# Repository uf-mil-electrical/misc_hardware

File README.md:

# misc_hardware
PCB stuff that doesn't belong to any specific robot

## Projects by type:
### Communication
- [Peter Feng] MCP2515 CAN Bus Module Testing

### LEDs
- [Erik Neff-Flahan] 8x8 Neopixel Matrix V1
- [Russell MacGregor] 8x8 Neopixel Matrix V2
- [Russell MacGregor] Neopixel Breakout Board
- [Erik Neff-Flahan] Neopixel RP2350 C Library

### Logic
- [Russell MacGregor] Level Shifter Breakout V1

### Navigation
- [Russell MacGregor] IMU Test Board V1 (incomplete)

### Power
- [Russell MacGregor] 3V3 1.5A Regulator Breakout
- [Russell MacGregor] Battery ORing Test Board V1
- [Erik Neff-Flahan] RobotX Buoy Board Power Setup
- [Russell MacGregor] Inductor Breakout V1
- [Russell MacGregor] MAX20408 Breakout V1
- [Russell MacGregor] TPS26631 E-Fuse Breakout V1

### RobotX2026
- [Aiden Shepler] Task 2 Props (underwater LEDs)

### Sensing
- [Russell MacGregor] Air Quality Monitor V1
- [Russell MacGregor] Atmospheric Monitor V1
- [Russell MacGregor] Door Sensor V3

### USB
- [Russell MacGregor] USB 2.0 Hub Breakout V4

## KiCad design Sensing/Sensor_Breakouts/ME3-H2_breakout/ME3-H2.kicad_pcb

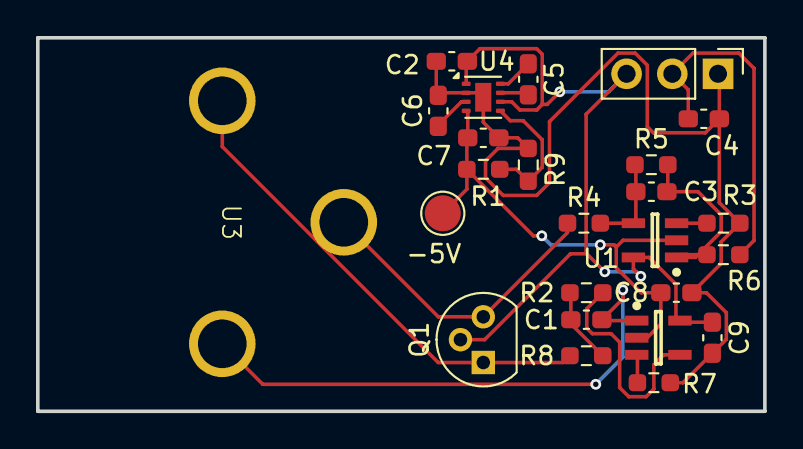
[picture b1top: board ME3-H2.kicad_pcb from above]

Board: 2 copper layers, 40.4 x 20.8 mm, 25 parts (0 on the bottom side), 17 nets.

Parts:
C1, C4, C8, C9: 0.1uF; C_0603_1608Metric_Pad1.08x0.95mm_HandSolder
C2, C3, C6: 4.7uF; C_0603_1608Metric_Pad1.08x0.95mm_HandSolder
C5: 1uF; C_0603_1608Metric_Pad1.08x0.95mm_HandSolder
C7: 2.2uF; C_0603_1608Metric_Pad1.08x0.95mm_HandSolder
J1: Conn_01x03_Pin; PinHeader_1x03_P2.54mm_Vertical
Q1: PJFET; TO-92
R1: 158k; R_0603_1608Metric_Pad0.98x0.95mm_HandSolder
R2, R3, R7, R8: 10k; R_0603_1608Metric_Pad0.98x0.95mm_HandSolder
R4: 47; R_0603_1608Metric_Pad0.98x0.95mm_HandSolder
R5: 30k; R_0603_1608Metric_Pad0.98x0.95mm_HandSolder
R6: 100k; R_0603_1608Metric_Pad0.98x0.95mm_HandSolder
R9: 51k; R_0603_1608Metric_Pad0.98x0.95mm_HandSolder
TP1: -5V; TestPoint_Pad_D2.0mm
U1, U2: LT6003HS5TRPBF; LT-S5-5-TSOT-23_N
U3: ME3-H2
U4: LM27761; WSON-8-1EP_2x2mm_P0.5mm_EP0.9x1.6mm

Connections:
+5V: C2.2, C9.2, J1.3, Q1.2 (G), U1.5 (V+), U2.5 (V+), U4.1 (VIN), U4.6 (EN)
-5V: C7.2, C8.2, R1.1, TP1.1, U1.2 (V-), U2.2 (V-), U4.4 (VOUT)
/Counter: C1.2, U2.1 (OUT), U3.3 (Counter)
/Reference: Q1.1 (D), R8.1, U3.2 (Reference)
/Vout: C4.2, J1.2, R6.2
/Working: Q1.3 (S), R4.1, U3.1 (Working)
GND: C2.1, C4.1, C6.2, C7.1, C8.1, C9.1, J1.1, R3.2, R7.2, R9.2, U4.2 (GND), U4.9 (PAD)
unnamed: C1.1, R2.1, R8.2
unnamed: R3.1, U1.3 (+IN)
unnamed: C3.1, R4.2, R5.1, U1.4 (-IN)
unnamed: C3.2, R5.2, R6.1, U1.1 (OUT)
unnamed: R7.1, U2.3 (+IN)
unnamed: R2.2, U2.4 (-IN)
unnamed: C5.1, U4.8 (C+)
unnamed: C5.2, U4.7 (C-)
unnamed: C6.1, U4.3 (CPOUT)
unnamed: R1.2, R9.1, U4.5 (VFB)

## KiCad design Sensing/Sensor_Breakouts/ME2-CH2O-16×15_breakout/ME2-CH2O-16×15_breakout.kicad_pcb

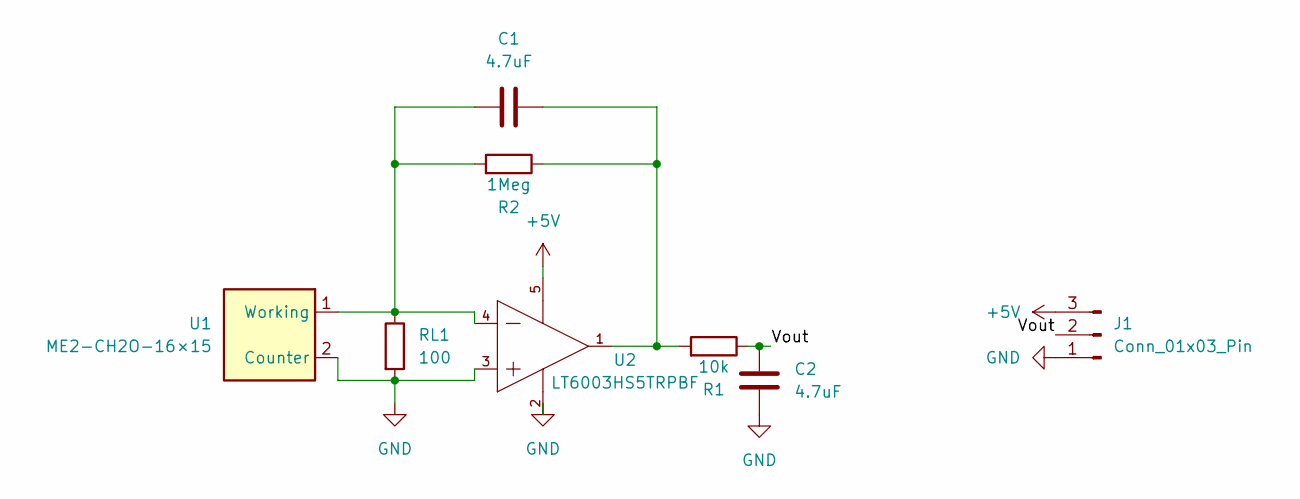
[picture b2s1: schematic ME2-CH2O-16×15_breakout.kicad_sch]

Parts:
C1, C2: 4.7uF; C_0603_1608Metric_Pad1.08x0.95mm_HandSolder
J1: Conn_01x03_Pin; PinHeader_1x03_P2.54mm_Vertical
R1: 10k; R_0603_1608Metric_Pad0.98x0.95mm_HandSolder
R2: 1Meg; R_0603_1608Metric_Pad0.98x0.95mm_HandSolder
RL1: 100; R_0603_1608Metric_Pad0.98x0.95mm_HandSolder
U1: ME2-CH2O-16×15
U2: LT6003HS5TRPBF; LT-S5-5-TSOT-23_N

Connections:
+5V: J1.3, U2.5 (V+)
/Vout: C2.2, J1.2, R1.1
GND: C2.1, J1.1, RL1.2, U1.2 (Counter), U2.2 (V-), U2.3 (+IN)
unnamed: C1.1, R2.2, RL1.1, U1.1 (Working), U2.4 (-IN)
unnamed: C1.2, R1.2, R2.1, U2.1 (OUT)

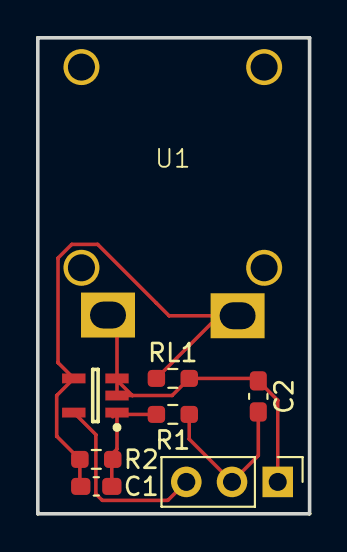
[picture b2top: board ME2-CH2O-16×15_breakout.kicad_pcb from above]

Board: 2 copper layers, 15.1 x 26.4 mm, 8 parts (0 on the bottom side), 5 nets.

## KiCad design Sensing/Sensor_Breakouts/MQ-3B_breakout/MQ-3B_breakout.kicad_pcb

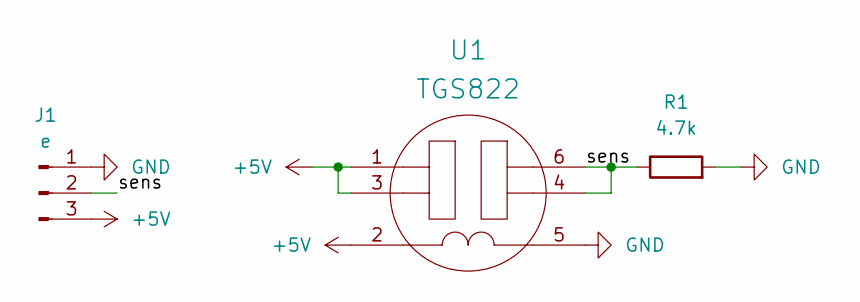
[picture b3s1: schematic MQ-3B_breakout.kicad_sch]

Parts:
J1: e; PinHeader_1x03_P2.54mm_Vertical
R1: 4.7k; R_Axial_DIN0207_L6.3mm_D2.5mm_P7.62mm_Horizontal
U1: TGS822; FP-TGS822-MFG

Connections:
+5V: J1.3, U1.1 (VC), U1.2 (VH), U1.3 (VC)
/sens: J1.2, R1.1, U1.4 (VRL), U1.6 (VRL)
GND: J1.1, R1.2, U1.5 (GND)

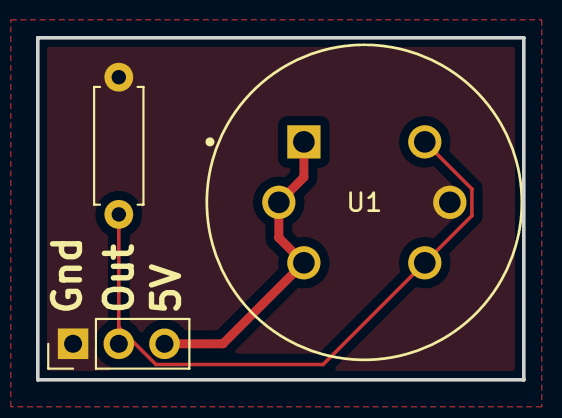
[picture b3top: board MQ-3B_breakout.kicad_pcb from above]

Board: 2 copper layers, 27.0 x 19.0 mm, 3 parts (0 on the bottom side), 3 nets.

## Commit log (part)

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2025-09-22 Finished Door Sensor Board V1
    ye
2025-09-29 09/29 Update
2025-10-08 Generated fabrication files
2025-11-09 Start working on Servo tester code
2025-11-13 Added SSD1306 drivers and tested it
2025-11-13 Cleaned up project, can now draw pulse on the screen
2025-12-04 completed revision of board
    - now uses Pico 2W instead of ESP-32 WROOM board
    - should resolve all issues
2025-12-05 Finalized BOM for ordering parts
2025-12-05 generated excel bom
2025-12-30 Started programming V2
2026-01-06 FINALLY FINALLY FINALLY TOF WORKS YAY
2026-01-06 deleted unnecessary files
2026-01-15 work in progress
2026-01-15 better work in progress
2026-01-15 readded non-wireless code back to repo
2026-01-15 last backup commit i promise
2026-01-15 just kidding last backup frfr
2026-01-15 started modification of CMakeList.txt
    works so far...
2026-01-15 updated CMakeTxt, haven't yet changed project name
2026-01-15 changed project name yay!
2026-01-15 changed file name
2026-01-15 created new file for BLE-relevant functions
    just don't include temp_sensor.h there, it doesn't like that
2026-01-15 untested but compiles
2026-01-16 Created advertisement broadcast design
2026-01-16 figuring things out!
2026-01-16 starting to rework functional program
2026-01-16 restarted cuz bluetooth le explorer is silly
2026-01-16 functional CMakelist file with all libraries and program files added in
2026-01-16 so far so good
2026-01-16 okokj
2026-01-16 possibly getting closer
2026-01-17 progress?
2026-01-19 closer and closer
2026-01-19 okok
2026-01-19 progress
2026-01-19 YESS FINALLY FREEDOM YAYAYAYAY
2026-01-20 starting to add dfplayer functionality to main program
2026-01-20 continued work
2026-02-12 started new pcb
2026-02-12 created main.py for rpi zero
2026-02-27 meow
2026-02-27 readded this stuff
2026-02-27 pushing changes
2026-03-04 Added draft of STM32 PCB template to be checked out before continuing.
2026-03-04 STM32F4 template added and ready for review
2026-03-05 worked on test boards
2026-03-14 created production files for all test boards
2026-03-15 Created 3x3 Template board, renamed old board to STM32 Pico
2026-03-15 updated gitignore
2026-03-31 recreated testing code
2026-03-31 progress on new pcb and code
2026-03-31 progress on board
2026-04-02 DOORDOORDOORDOORDOOR
2026-04-04 moved reference designs to mil-altium
2026-04-10 ordered
2026-04-10 started board
2026-04-13 created inductor breakout
2026-04-16 progress on code
2026-04-17 generated fab files
2026-04-18 progress on code!
2026-04-20 working yippee
2026-04-20 added spreadsheet version of door-sense-v3 bom
2026-04-20 updated bom
2026-05-02 minor change to usb hub v1
2026-05-02 renamed usb hub from v2 to v1
2026-05-02 work started on usb breakout v2
2026-05-04 added range checking to door sense codew
2026-05-05 increased delay on startup to give dfplayer more time to init
2026-05-12 5/12 "Awesome Super Cool NeoPixel Library"
    Start of neopixel library. More functions to be added soon!
2026-05-14 5/13 Readme added and start of tweaks to functions
    - Added readme file w/ start of documentation
    - Tweaking functions to get them easily useable in other projects
2026-05-14 5/14 README updates, main code updates
    - Updated README file to contain more info on the file structure/relevant files
    - modified example section of the code and some funcitons
2026-05-15 5/15 Start of NeoPix. Matrix PCB
    Also started investigating the Alitum multi-channel design docs to help with the creation of this file
    README contains info on (future) reasons for elements present in design.
2026-05-16 5/16 up to routing
    rooms made, now moving on to routing
2026-05-17 5/16 more progress on pcb
    added polygon pours about to update classes
2026-05-17 5/16 fixed viaas
2026-05-17 5/17 Board done*
    Finished polygons, board layout, and screw holes. Fixed routing issue with manual changes to the netlists, this will break if the schematics is updated.
    * done unless objections by other members, awaiting inspection
2026-05-17 5/17 Manufacturing Files and BOM
2026-05-22 5/22 Smaller neopixel board
    Camtastic files include Gerber files and NC drill files
2026-05-26 added rgb led
2026-06-01 progress on atmospheric monitoring board
2026-06-03 created prod files for atmo mon v1
2026-06-04 progress on usb board
2026-06-10 USB Hub work
2026-06-12 Generated production files for USB Hub V3 test board
2026-06-12 removed 47uf caps, regenerated production files
    I removed the capacitor bank because I was concerned about inrush current when the battery is connected to the sub battery tube board stack / neopixel board.
2026-06-30 Add my local file
